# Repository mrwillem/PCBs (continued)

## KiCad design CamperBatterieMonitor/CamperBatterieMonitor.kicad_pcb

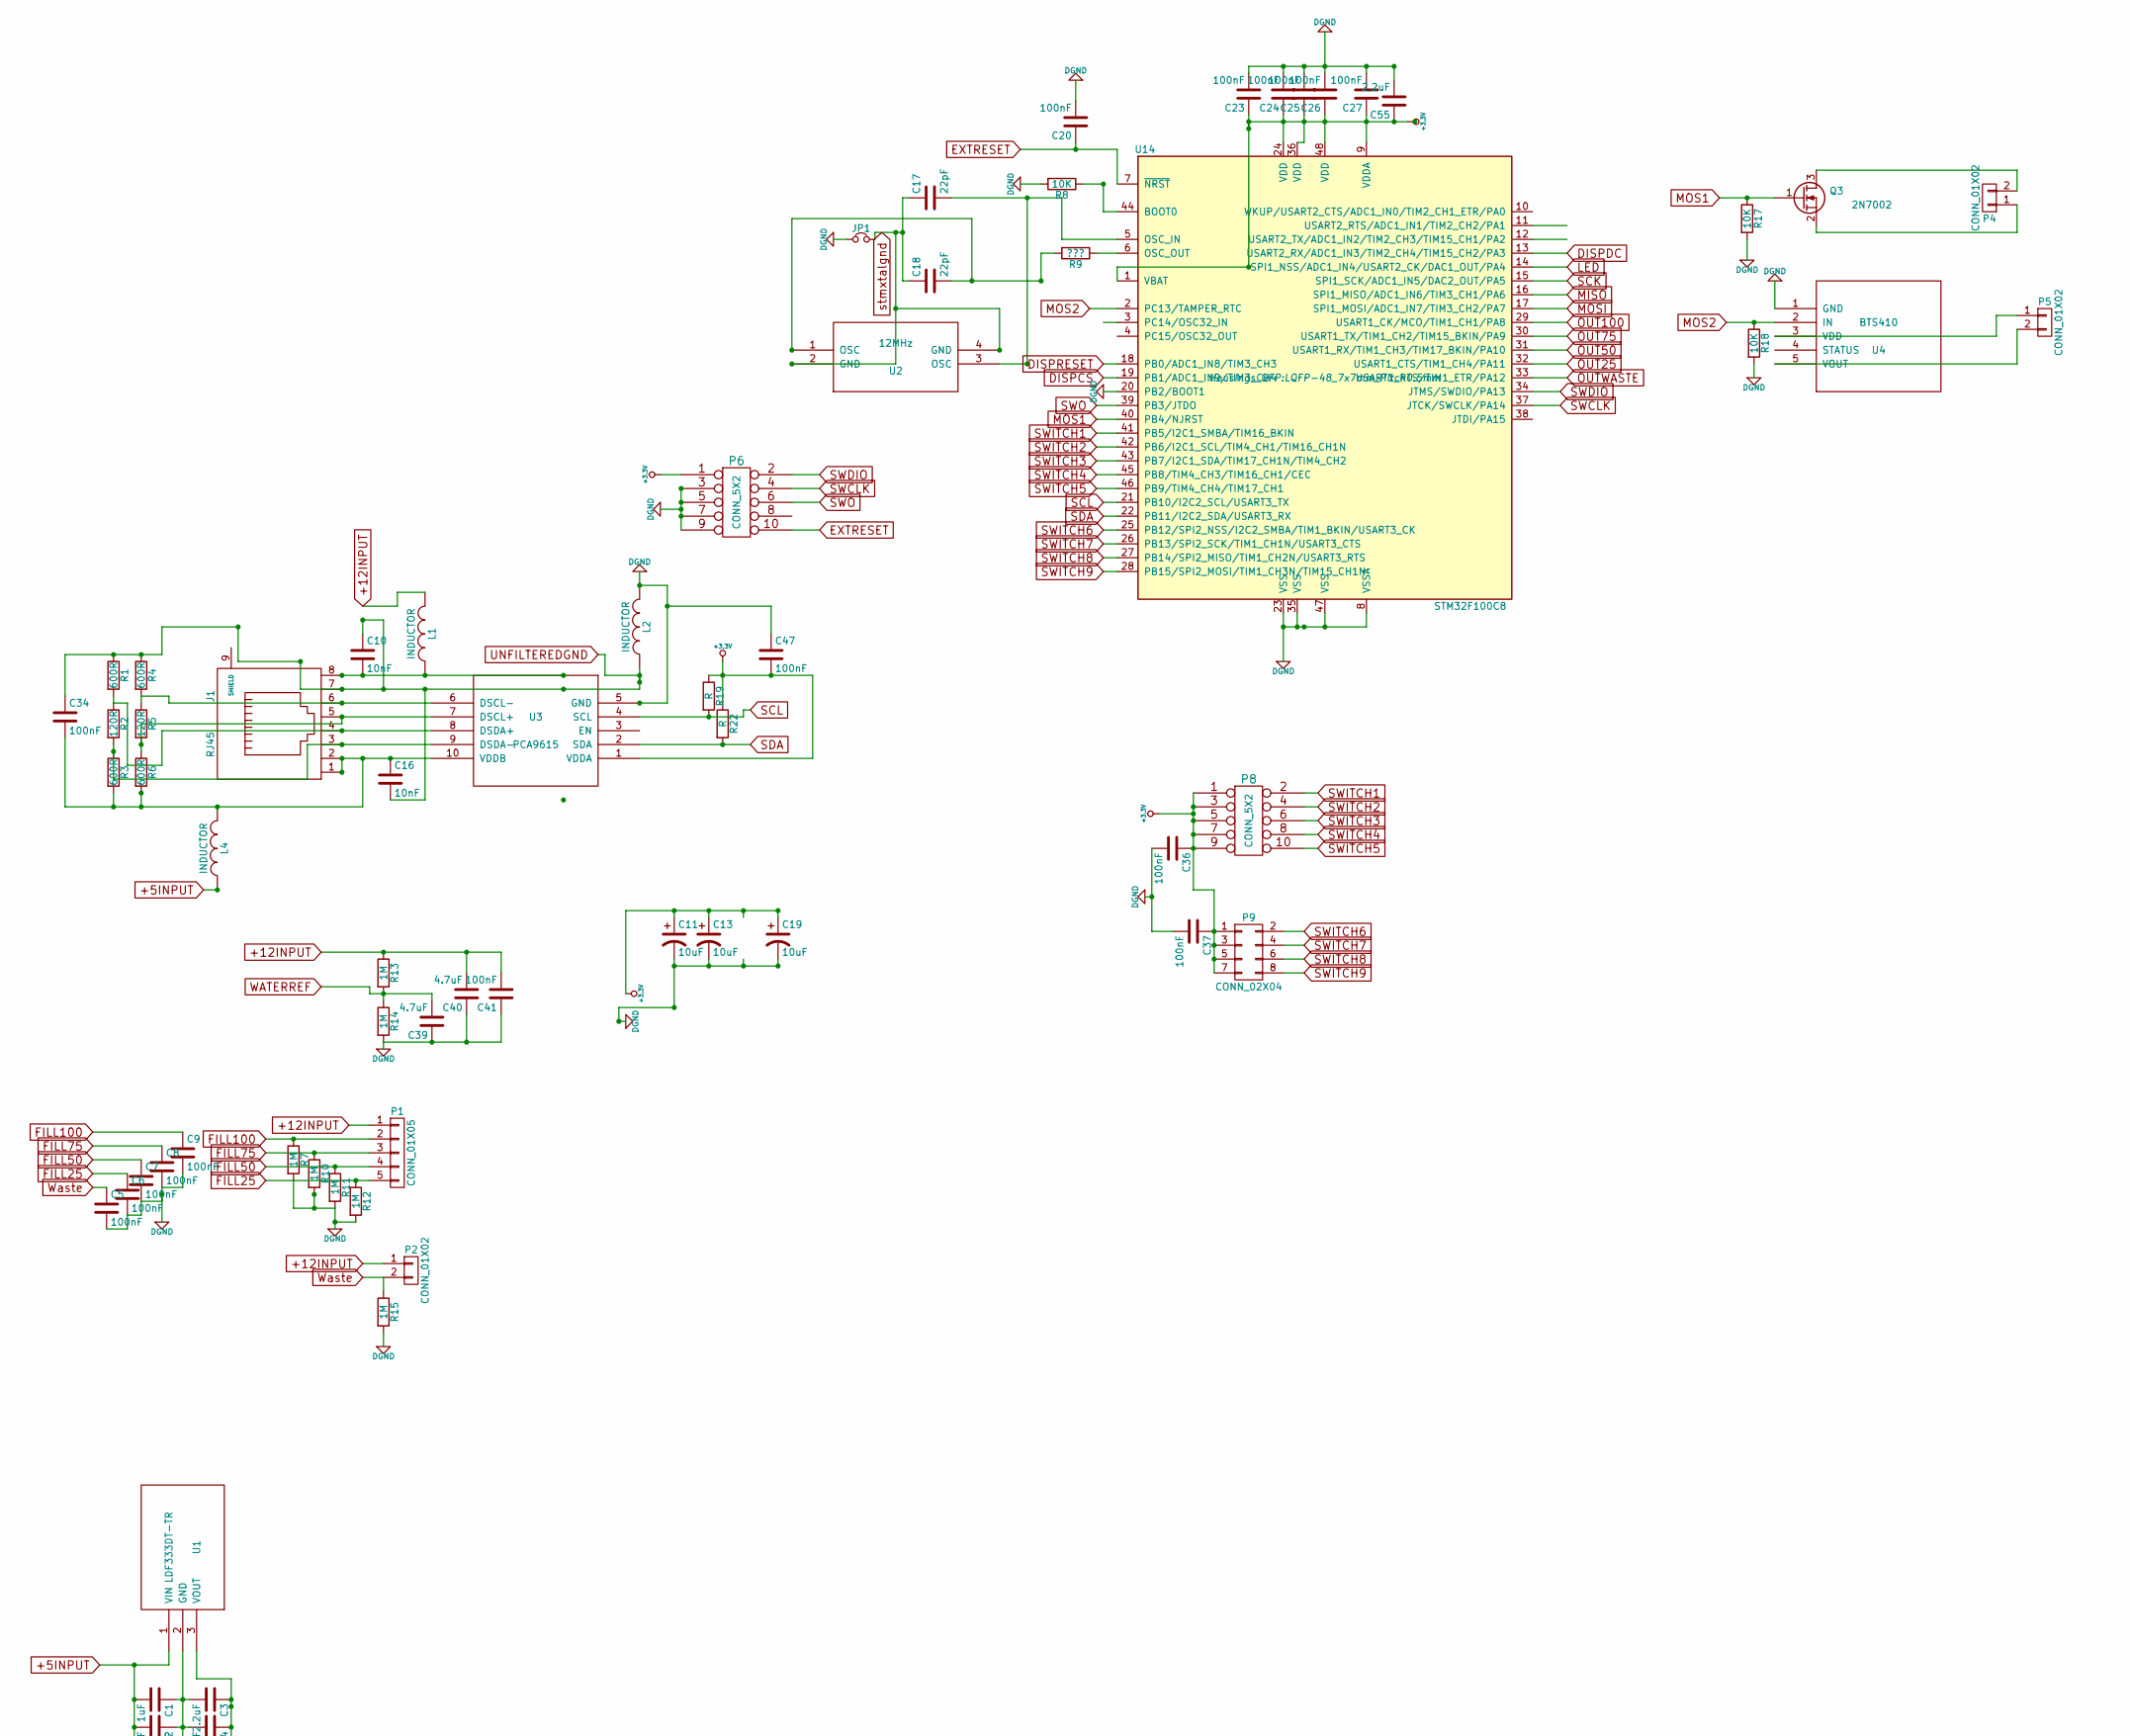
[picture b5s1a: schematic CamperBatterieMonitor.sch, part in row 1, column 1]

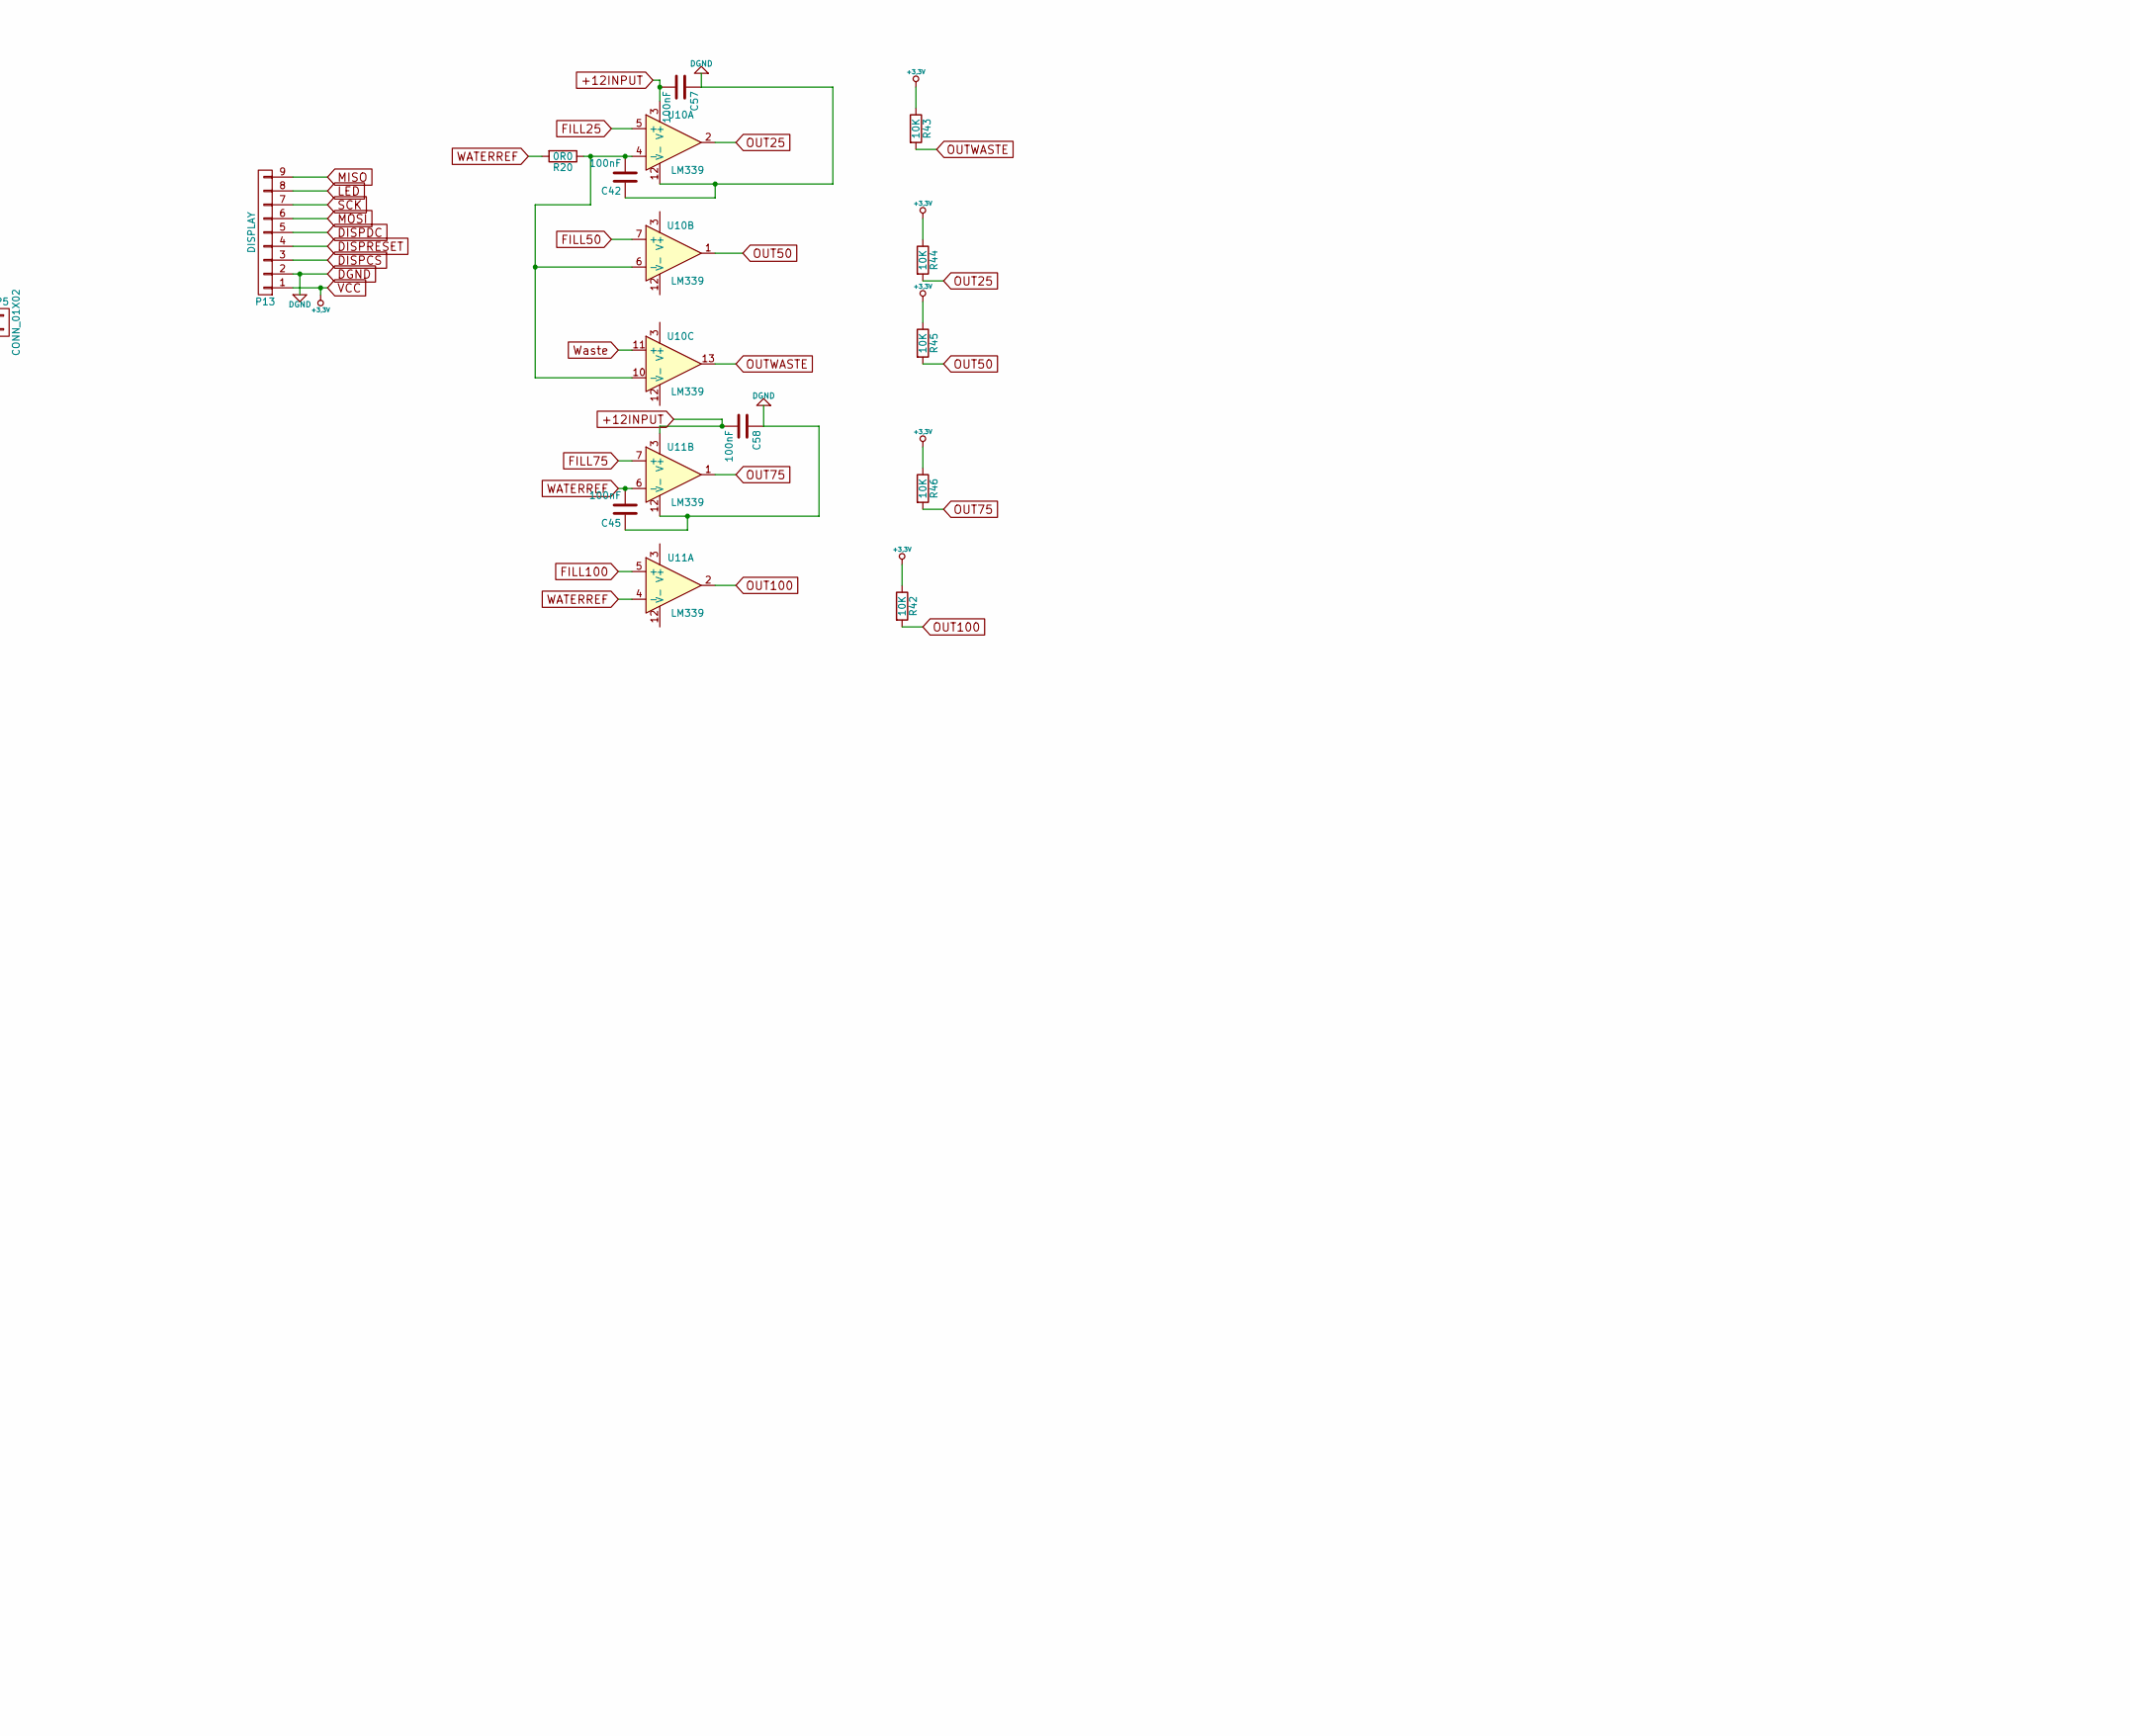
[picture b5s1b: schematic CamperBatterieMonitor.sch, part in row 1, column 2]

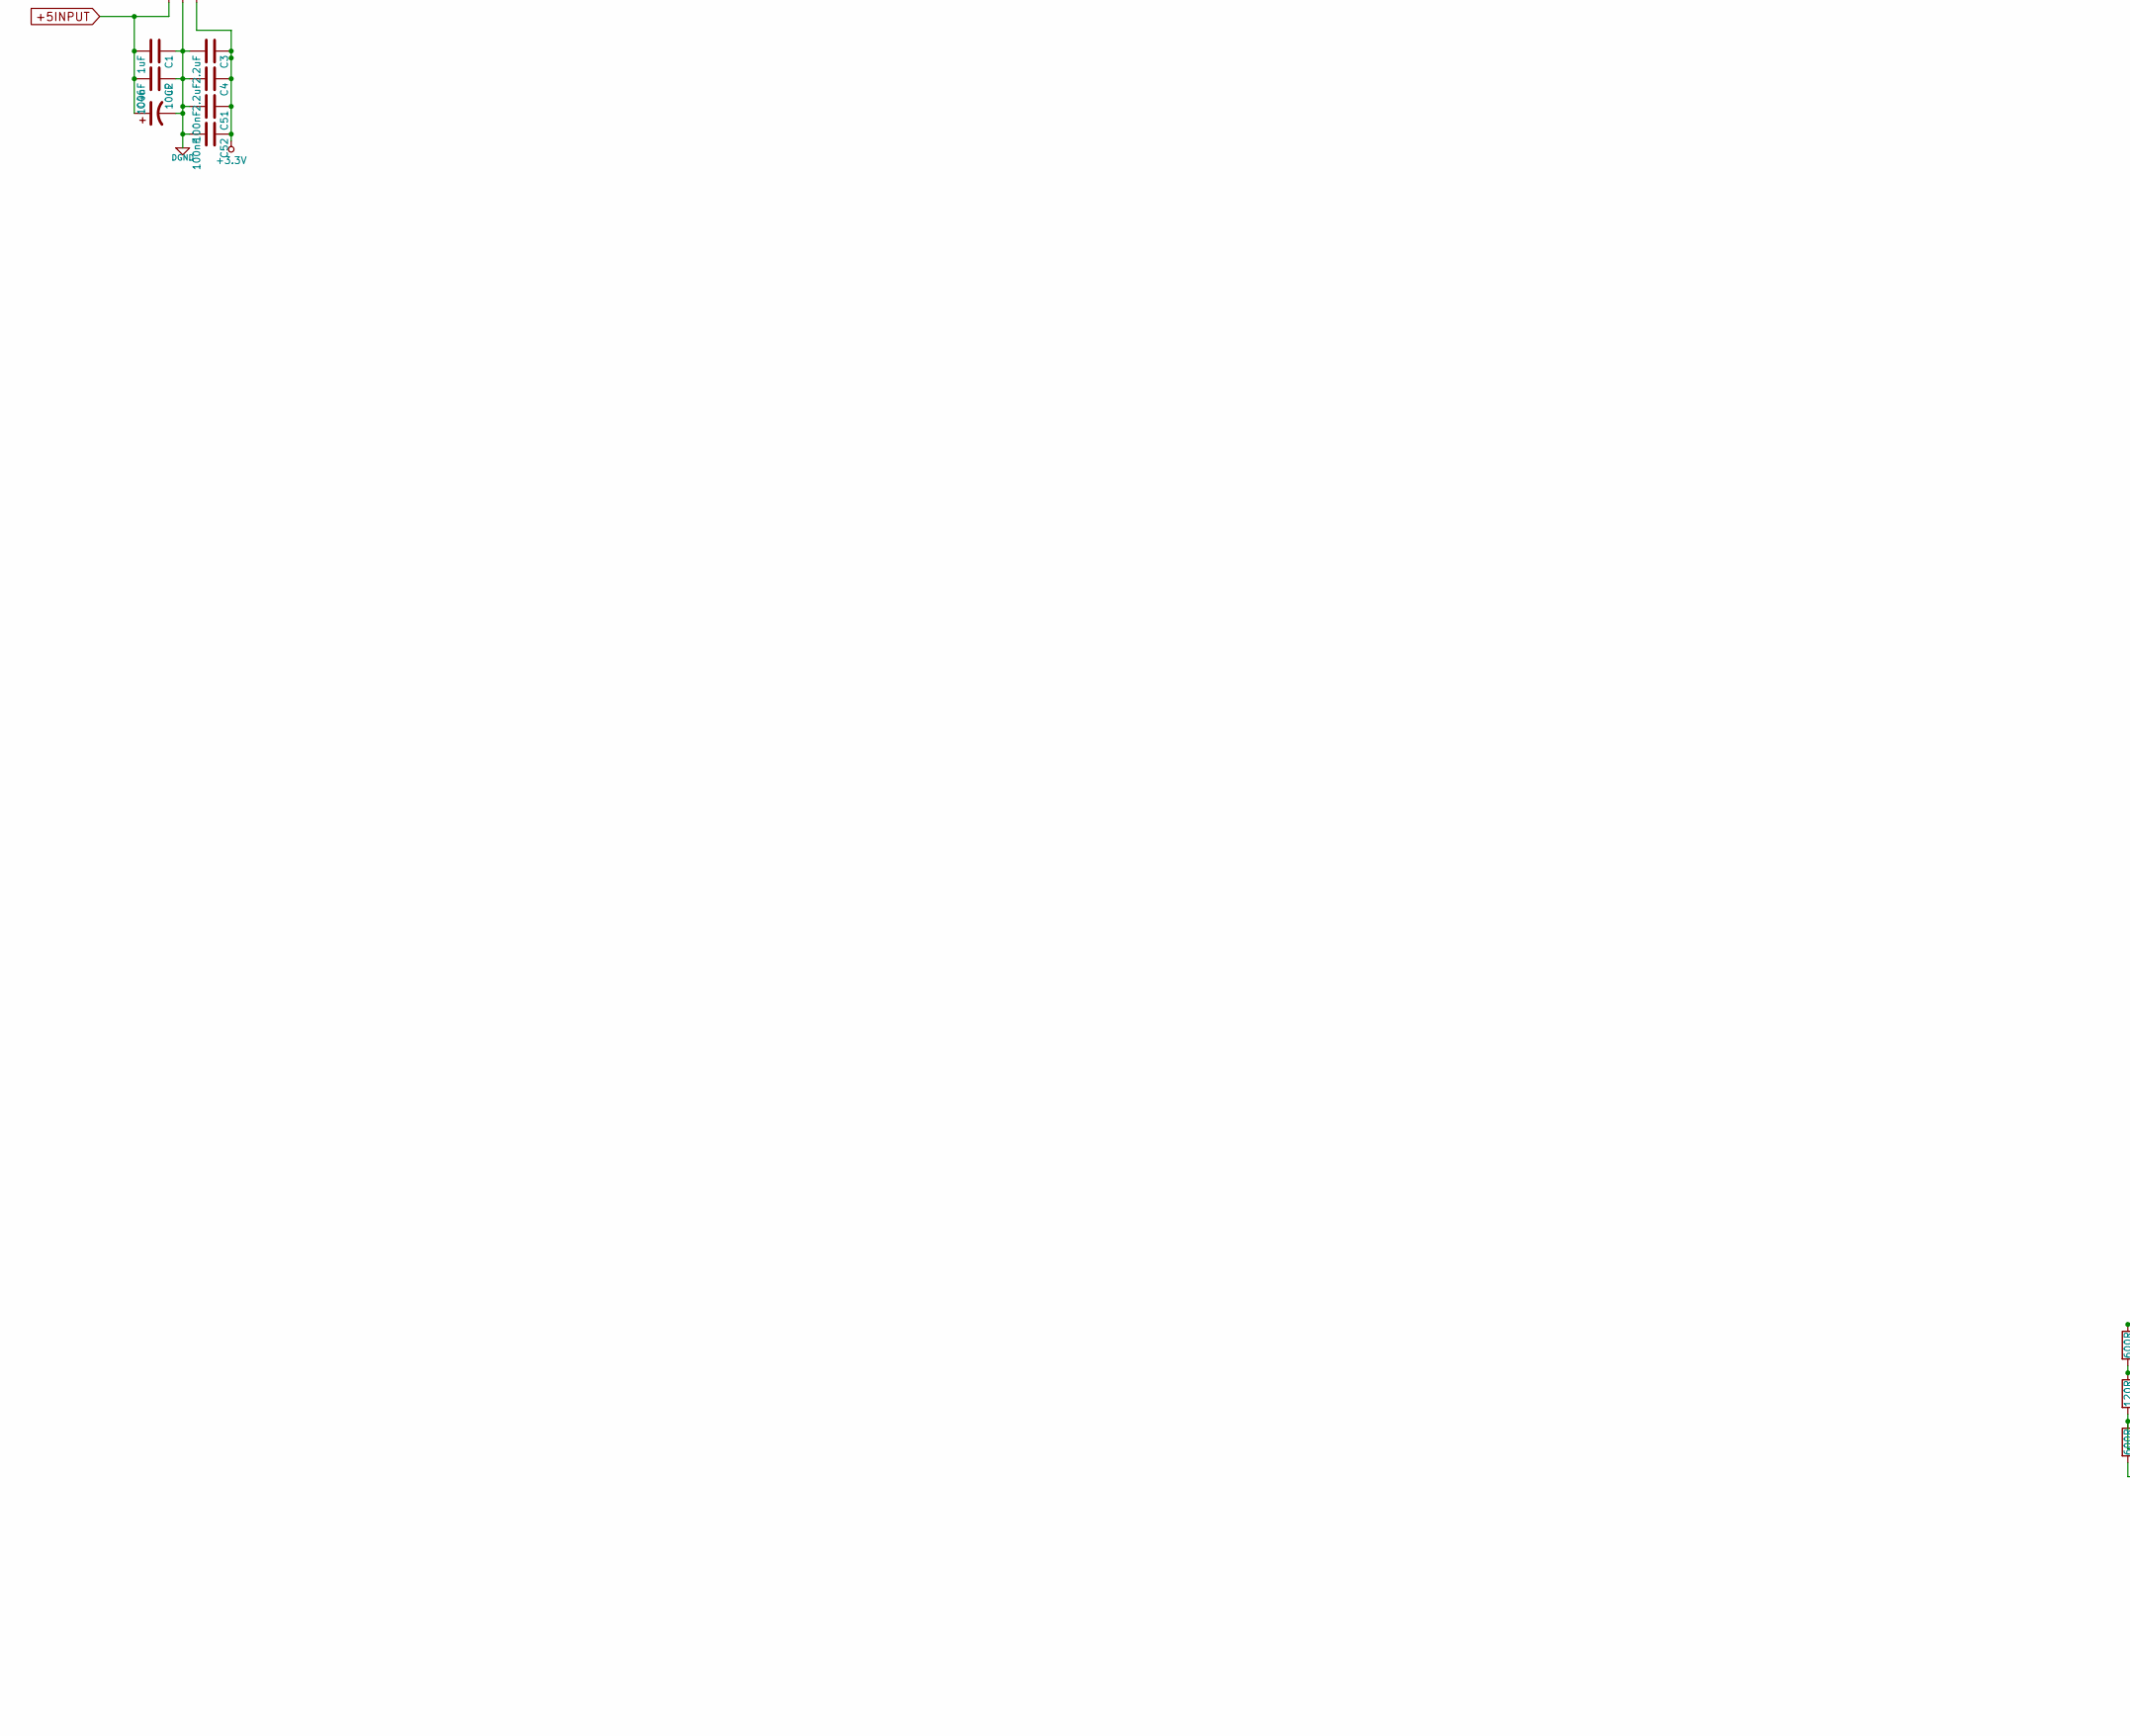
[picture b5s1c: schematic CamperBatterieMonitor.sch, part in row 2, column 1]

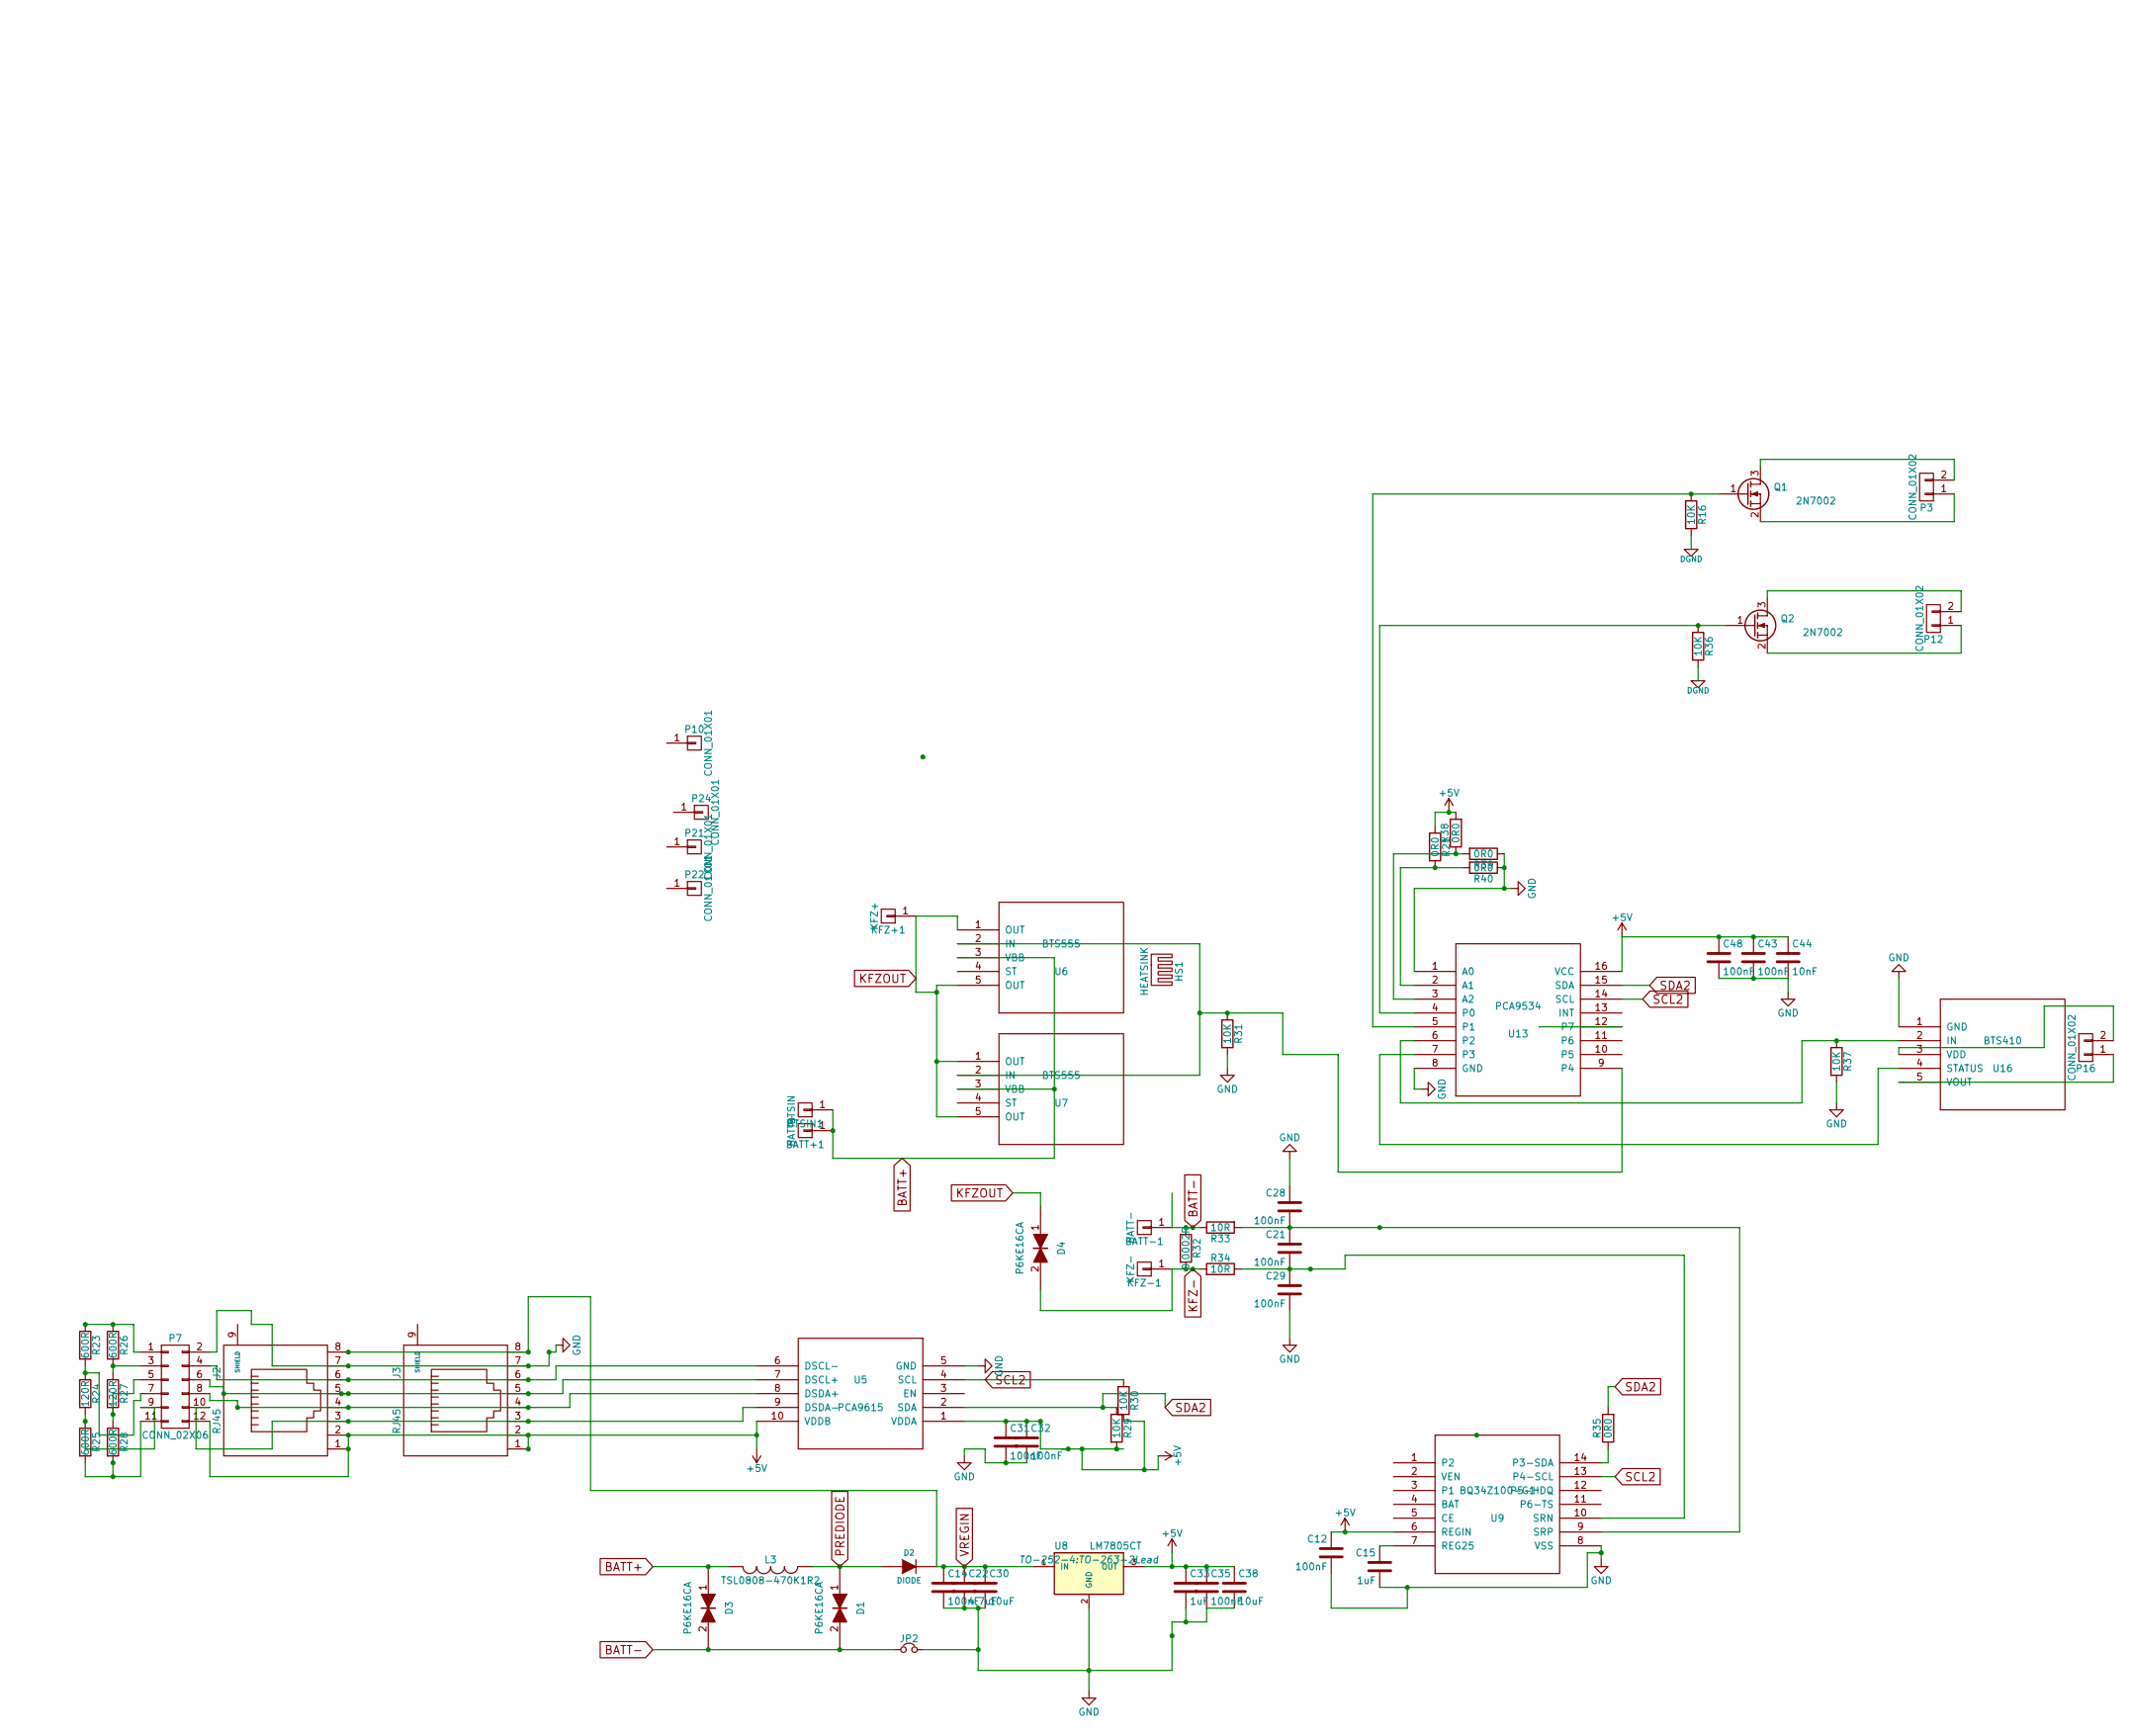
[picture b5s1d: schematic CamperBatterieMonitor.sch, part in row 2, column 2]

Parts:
BATT+1: BATT+; WE_threaded_shank_M5_160A
BATT-1: BATT-; WE_threaded_shank_M5_160A
BTSIN1: BTSIN; WE_threaded_shank_M5_160A
C1, C15, C33: 1uF; C_0805
C2, C5, C6, C7, C8, C9, C12, C14, C20, C21, C23, C24, C25, C26, C27, C28, C29, C31, C32, C34, C35, C36, C37, C41, C42, C43, C45, C47, C48, C51, C52, C57, C58: 100nF; C_0805
C3, C4: 2.2uF; C_0805
C10, C16, C44: 10nF; C_0805
C11, C13: 10uF; C_0805
C17, C18: 22pF; C_0805
C19, C38, C46: 10uF; c_elec_4x5.8
C22: 4,7uF; C_1812
C30: 10uF; C_1812
C39, C40: 4.7uF; C_1812
C55: 2,2uF; C_0805
D1, D3, D4: P6KE16CA; Diode_DO-201AD_Horizontal_RM15
D2: DIODE; SMA_Handsoldering
HS1: HEATSINK; Heatsink_Fischer_SK129-STS_42x25mm_2xDrill2.5mm
J1, J2, J3: RJ45; RJ45_8
JP1, JP2: Jumper_NC_Small; NetTie-I_Connected_SMD
KFZ+1: KFZ+; WE_threaded_shank_M5_160A
KFZ-1: KFZ-; WE_threaded_shank_M5_160A
L1, L2, L4: INDUCTOR; C_0805_HandSoldering
L3: TSL0808-470K1R2; C_Radial_D10_L16_P5
P1: CONN_01X05; weidmueller_5
P2, P3, P4, P5, P12, P16: CONN_01X02; weidmueller_2
P6: CONN_5X2; Pin_Header_Straight_2x05_Pitch1.27mm
P7: CONN_02X06; Pin_Header_Straight_2x06
P8: CONN_5X2; weidmueller_10
P9: CONN_02X04; Pin_Header_Straight_2x04_Pitch1.27mm
P10, P21, P22, P24: CONN_01X01; hole
P13: DISPLAY; 2.2inchQVGASPIwithStorage
Q1, Q2, Q3: 2N7002; SOT-23
R1, R3, R4, R6, R23, R25, R26, R28: 600R; R_0805_HandSoldering
R2, R5, R24, R27: 120R; R_0805_HandSoldering
R7, R10, R11, R12, R13, R14, R15: 1M; R_1206
R8, R16, R17, R18, R29, R30, R31, R36, R37, R42, R43, R44, R45, R46: 10K; R_0805_HandSoldering
R9: ???; R_0603_HandSoldering
R19, R22: R; R_0805_HandSoldering
R20: 0R0; R_1206_HandSoldering
R21, R38, R39, R40: 0R0; R_0603
R32: 0.0002R; WSLP_5931_DALE
R33, R34: 10R; R_0805_HandSoldering
R35: 0R0; R_0805_HandSoldering
U1: LDF333DT-TR; TO-252-2Lead
U2: 12MHz; Xtal_Ceramic_5x3.2
U3, U5: PCA9615; TSSOP-10_3x3mm_Pitch0.5mm
U4, U16: BTS410; TO-263-5Lead
U6, U7: BTS555; TO218-5
U8: LM7805CT; TO-263-2Lead
U9: BQ34Z100-G1; TSSOP-14_4.4x5mm_Pitch0.65mm
U10, U11: LM339; SOIC-14_3.9x8.7mm_Pitch1.27mm
U13: PCA9534; SOIC-16_7.5x10.3mm_Pitch1.27mm
U14: STM32F100C8; LQFP-48_7x7mm_Pitch0.5mm

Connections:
+5INPUT: C1.2, C2.2, C46.1, L4.1, U1.1 (VIN)
+5V: C12.1, C31.1, C32.1, C33.1, C35.1, C38.1, C43.1, C44.1, C48.1, J2.1, J2.2, J3.1, J3.2, P7.12, R21.1, R29.2, R30.2, R38.2, U5.1 (VDDA), U5.10 (VDDB), U8.3 (OUT), U9.6 (REGIN), U13.16 (VCC)
+12INPUT: C40.2, C41.2, C57.2, C58.2, L1.2, P1.1, P2.1, R13.1, U10.3 (V+), U11.3 (V+)
BATT+: BATT+1.1, BTSIN1.1, D3.1, L3.2, U6.3 (VBB), U7.3 (VBB)
BATT-: BATT-1.1, D1.2, D3.2, JP2.1, R32.1, R33.1
DGND: C1.1, C2.1, C3.2, C4.2, C5.2, C6.2, C7.2, C8.2, C9.2, C11.2, C13.2, C19.2, C20.2, C23.2, C24.2, C25.2, C26.2, C27.2, C36.2, C37.2, C39.1, C40.1, C41.1, C42.1, C45.1, C46.2, C47.1, C51.2, C52.2, C55.2, C57.1, C58.1, JP1.1, L2.2, P6.3, P6.5, P6.7, P6.9, P13.2, R7.2, R8.2, R10.2, R11.2, R12.2, R14.2, R15.2, R16.2, R17.2, R18.2, R36.2, U1.2 (GND), U3.5 (GND), U4.1 (GND), U10.12 (V-), U11.12 (V-), U14.8 (VSSA), U14.20 (PB2/BOOT1), U14.23 (VSS), U14.35 (VSS), U14.47 (VSS)
DISPCS: P13.3, U14.19 (PB1/ADC1_IN9/TIM3_CH4)
DISPDC: P13.5, U14.13 (USART2_RX/ADC1_IN3/TIM2_CH4/TIM15_CH2/P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)
DISPRESET: P13.4, U14.18 (PB0/ADC1_IN8/TIM3_CH3)
EXTRESET: C20.1, P6.10, U14.7 (~NRST)
FILL25: C6.1, P1.5, R12.1, U10.5 (+)
FILL50: C7.1, P1.4, R11.1, U10.7 (+)
FILL75: C8.1, P1.3, R10.1, U11.7 (+)
FILL100: C9.1, P1.2, R7.1, U11.5 (+)
GND: C12.2, C14.2, C15.2, C22.2, C28.1, C29.2, C30.2, C31.2, C32.2, C33.2, C35.2, C38.2, C43.2, C44.2, C48.2, J2.7, J3.7, JP2.2, P7.2, R31.2, R37.2, R39.1, R40.1, U5.5 (GND), U8.2 (GND), U9.8 (VSS), U13.1 (A0), U13.8 (GND), U16.1 (GND)
KFZ-: D4.2, KFZ-1.1, R32.2, R34.2
KFZOUT: D4.1, KFZ+1.1, U6.1 (OUT), U6.5 (OUT), U7.1 (OUT), U7.5 (OUT)
LED: P13.8, U14.14 (SPI1_NSS/ADC1_IN4/USART2_CK/DAC1_OUT/PA4)
MISO: P13.9, U14.16 (SPI1_MISO/ADC1_IN6/TIM3_CH1/PA6)
MOS1: Q3.1 (G), R17.1, U14.40 (PB4/NJRST)
MOS2: R18.1, U4.2 (IN), U14.2 (PC13/TAMPER_RTC)
MOSI: P13.6, U14.17 (SPI1_MOSI/ADC1_IN7/TIM3_CH2/PA7)
unnamed: C10.2, J1.8, L1.1
unnamed: C15.1, U9.7 (REG25)
unnamed: C16.1, C34.2, J1.1, J1.2, L4.2, R3.2, R6.2, U3.10 (VDDB)
unnamed: C17.2, U2.3 (OSC), U14.5 (OSC_IN)
unnamed: C18.2, R9.2, U2.1 (OSC)
unnamed: C21.1, C28.2, R33.2, U9.9 (SRP)
unnamed: C21.2, C29.1, R34.1, U9.10 (SRN)
unnamed: C42.2, R20.1, U10.4 (-), U10.6 (-), U10.10 (-)
unnamed: J1.3, R2.2, R3.1, U3.9 (DSDA-)
unnamed: J1.4, R1.2, R2.1, U3.8 (DSDA+)
unnamed: J1.5, R5.2, R6.1, U3.7 (DSCL+)
unnamed: J1.6, R4.2, R5.1, U3.6 (DSCL-)
unnamed: J2.3, J3.3, P7.10, U5.9 (DSDA-)
unnamed: J2.4, J3.4, P7.8, U5.8 (DSDA+)
unnamed: J2.5, J3.5, P7.6, U5.7 (DSCL+)
unnamed: J2.6, J3.6, P7.4, U5.6 (DSCL-)
unnamed: P3.1, Q1.2 (S)
unnamed: P3.2, Q1.3 (D)
unnamed: P4.1, Q3.2 (S)
unnamed: P4.2, Q3.3 (D)
unnamed: P5.1, U4.3 (VDD)
unnamed: P5.2, U4.5 (VOUT)
unnamed: P7.1, R23.1, R26.1
unnamed: P7.3, R26.2, R27.1
unnamed: P7.5, R27.2, R28.1
unnamed: P7.7, R23.2, R24.1
unnamed: P7.9, R24.2, R25.1
unnamed: P7.11, R25.2, R28.2
unnamed: P12.1, Q2.2 (S)
unnamed: P12.2, Q2.3 (D)
unnamed: P16.1, U16.5 (VOUT)
unnamed: P16.2, U16.3 (VDD)
unnamed: Q1.1 (G), R16.1, U13.5 (P1)
unnamed: Q2.1 (G), R36.1, U13.4 (P0)
unnamed: R8.1, U14.44 (BOOT0)
unnamed: R9.1, U14.6 (OSC_OUT)
unnamed: R21.2, R40.2, U13.2 (A1)
unnamed: R31.1, U6.2 (IN), U7.2 (IN), U13.9 (P4)
unnamed: R35.1, U9.14 (P3-SDA)
unnamed: R37.1, U13.6 (P2), U16.2 (IN)
unnamed: R38.1, R39.2, U13.3 (A2)
unnamed: U13.7 (P3), U16.4 (STATUS)
OUT25: R44.2, U10.2, U14.32 (USART1_CTS/TIM1_CH4/PA11)
OUT50: R45.2, U10.1, U14.31 (USART1_RX/TIM1_CH3/TIM17_BKIN/PA10)
OUT75: R46.2, U11.1, U14.30 (USART1_TX/TIM1_CH2/TIM15_BKIN/PA9)
OUT100: R42.2, U11.2, U14.29 (USART1_CK/MCO/TIM1_CH1/PA8)
OUTWASTE: R43.2, U10.13, U14.33 (USART1_RTS/TIM1_ETR/PA12)
PREDIODE: D1.1, D2.1 (A), L3.1
SCK: P13.7, U14.15 (SPI1_SCK/ADC1_IN5/DAC2_OUT/PA5)
SCL: R19.2, U3.4 (SCL), U14.21 (PB10/I2C2_SCL/USART3_TX)
SCL2: R30.1, U5.4 (SCL), U9.13 (P4-SCL), U13.14 (SCL)
SDA: R22.2, U3.2 (SDA), U14.22 (PB11/I2C2_SDA/USART3_RX)
SDA2: R29.1, R35.2, U5.2 (SDA), U13.15 (SDA)
SWCLK: P6.4, U14.37 (JTCK/SWCLK/PA14)
SWDIO: P6.2, U14.34 (JTMS/SWDIO/PA13)
SWITCH1: P8.2, U14.41 (PB5/I2C1_SMBA/TIM16_BKIN)
SWITCH2: P8.4, U14.42 (PB6/I2C1_SCL/TIM4_CH1/TIM16_CH1N)
SWITCH3: P8.6, U14.43 (PB7/I2C1_SDA/TIM17_CH1N/TIM4_CH2)
SWITCH4: P8.8, U14.45 (PB8/TIM4_CH3/TIM16_CH1/CEC)
SWITCH5: P8.10, U14.46 (PB9/TIM4_CH4/TIM17_CH1)
SWITCH6: P9.2, U14.25 (PB12/SPI2_NSS/I2C2_SMBA/TIM1_BKIN/USART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)
SWITCH7: P9.4, U14.26 (PB13/SPI2_SCK/TIM1_CH1N/USART3_CTS)
SWITCH8: P9.6, U14.27 (PB14/SPI2_MISO/TIM1_CH2N/USART3_RTS)
SWITCH9: P9.8, U14.28 (PB15/SPI2_MOSI/TIM1_CH3N/TIM15_CH1N)
SWO: P6.6, U14.39 (PB3/JTDO)
UNFILTEREDGND: C10.1, C16.2, C34.1, J1.7, L2.1, R1.1, R4.1
VREGIN: C14.1, C22.1, C30.1, D2.2 (K), J2.8, J3.8, U8.1 (IN)
WATERREF: C39.2, C45.2, R13.2, R14.1, R20.2, U11.4 (-), U11.6 (-)
Waste: C5.1, P2.2, R15.1, U10.11 (+)
stmxtalgnd: C17.1, C18.1, JP1.2, U2.2 (GND), U2.4 (GND)

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
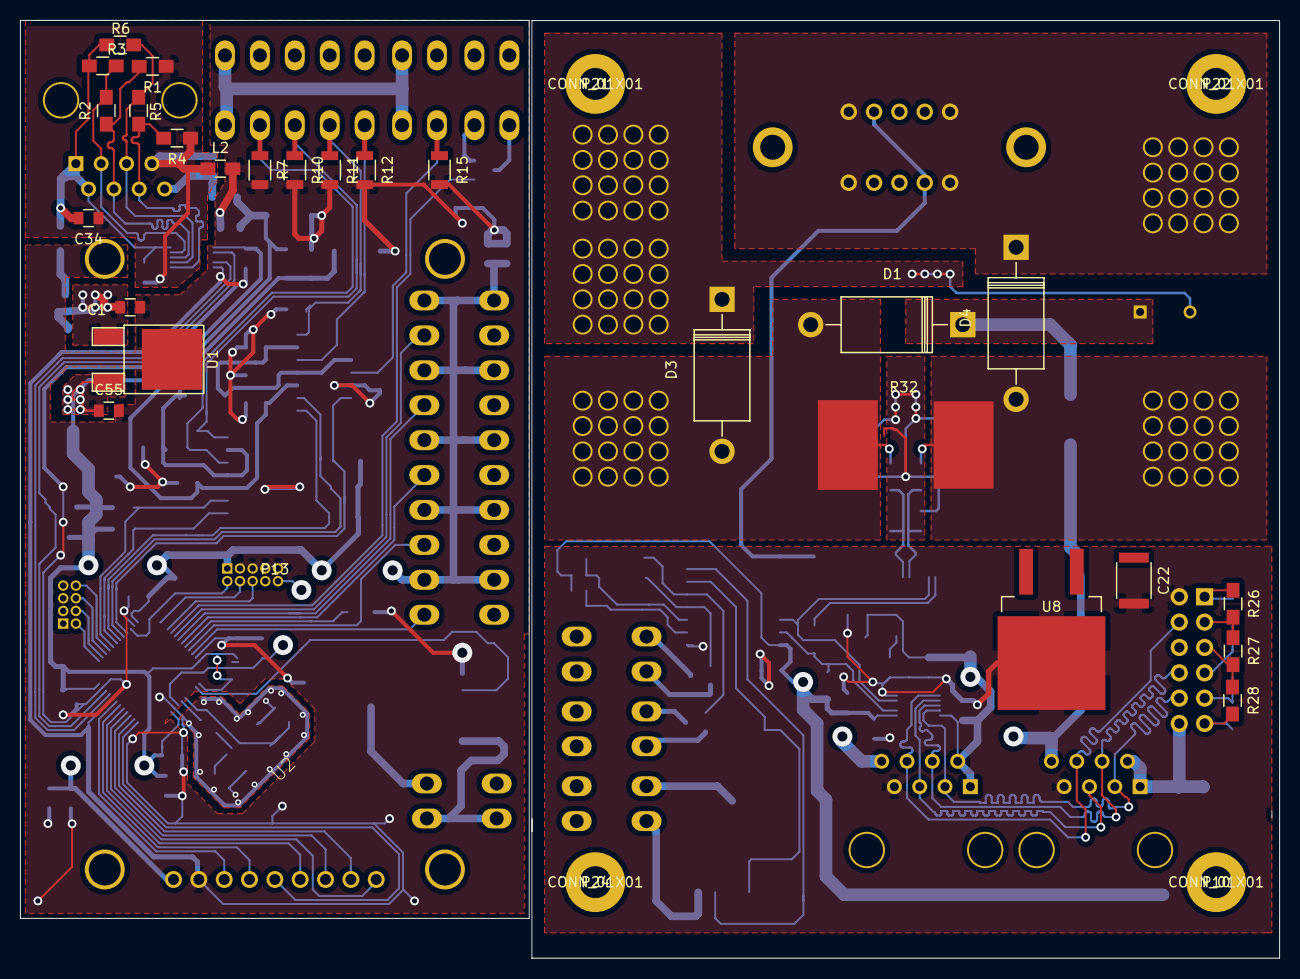
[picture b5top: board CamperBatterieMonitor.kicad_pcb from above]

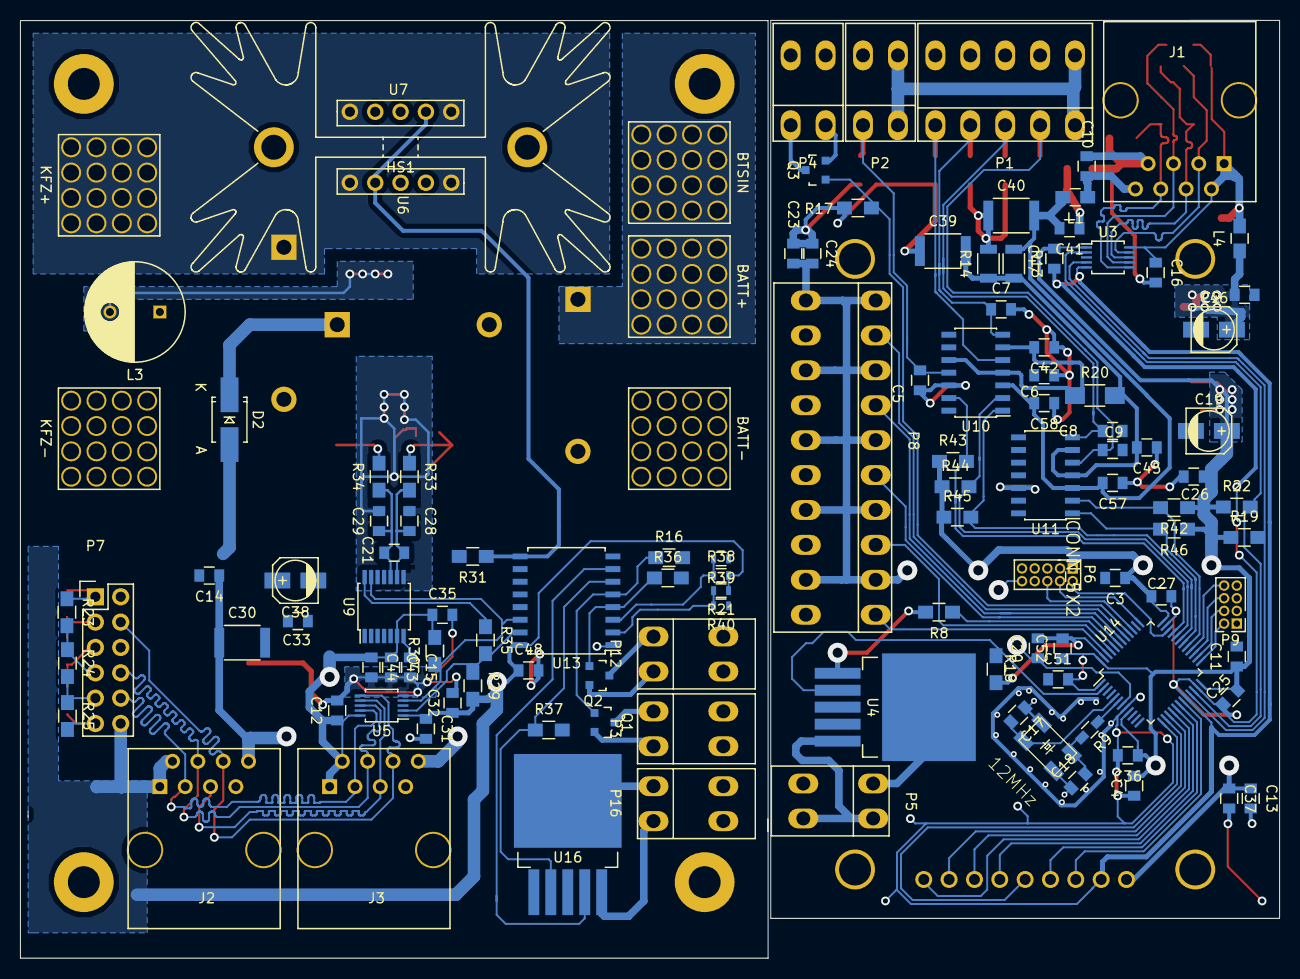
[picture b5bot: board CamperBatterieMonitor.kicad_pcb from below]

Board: 4 copper layers, 126.2 x 94.0 mm, 150 parts (119 on the bottom side), 93 nets.
